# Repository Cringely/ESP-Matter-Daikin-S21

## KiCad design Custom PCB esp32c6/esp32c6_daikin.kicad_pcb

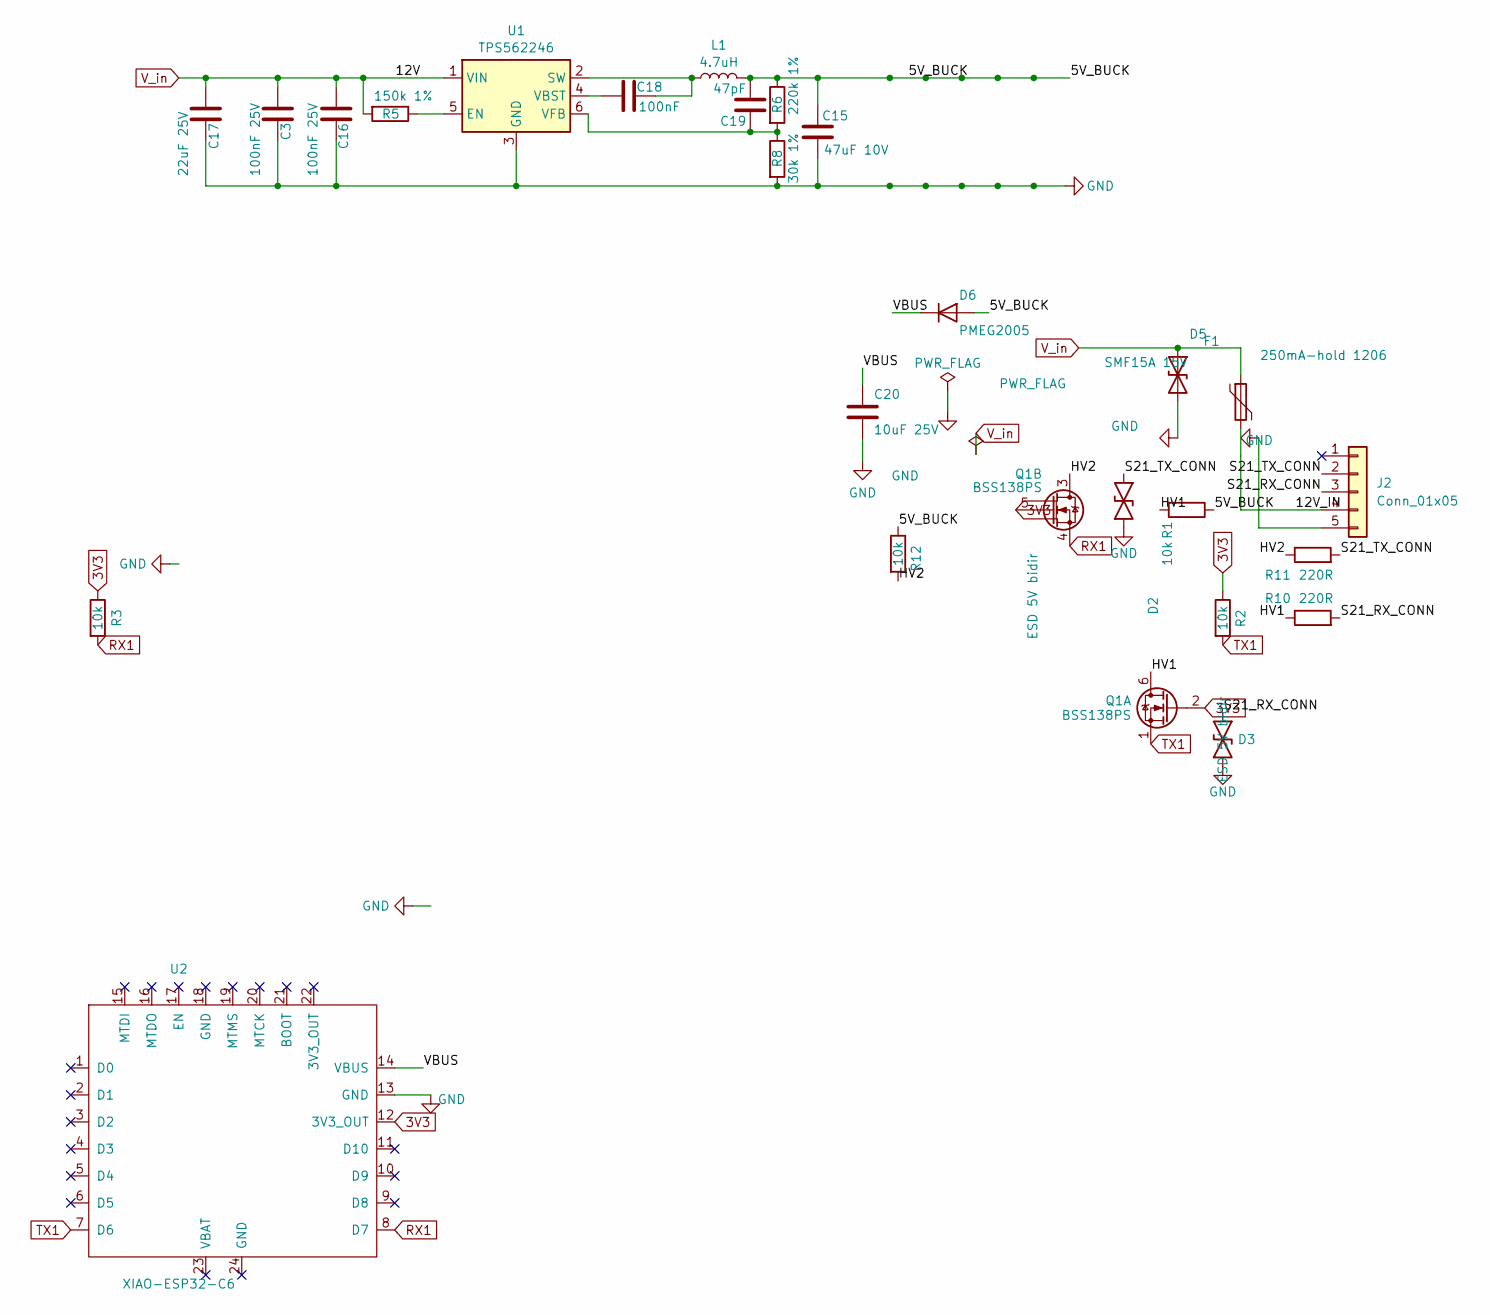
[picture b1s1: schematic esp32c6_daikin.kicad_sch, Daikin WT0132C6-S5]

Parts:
C3, C16: 100nF 25V; C0402; LCSC C307331
C15: 47uF 10V; C0805; LCSC C2292827
C17: 22uF 25V; C0805; LCSC C398931
C18: 100nF; C0402; LCSC C1525
C19: 47pF; C0402; LCSC C84706
C20: 10uF 25V; C0805; LCSC C15850
D2, D3: ESD 5V bidir; DFN1006-2L_L1.0-W0.6-P0.65-BI; MPN C5137770; LCSC C5137770
D5: SMF15A 15V; D_SOD-123F; LCSC C123802
D6: PMEG2005; D_SOD-123; LCSC C96233
F1: 250mA-hold 1206; Fuse_1206_3216Metric; LCSC C99561
J2: Conn_01x05; JST_EH_S5B-EH_1x05_P2.50mm_Horizontal; LCSC C265103
L1: 4.7uH; IND-SMD_L4.9-W4.9_NRS50XX; LCSC C307876
Q1: BSS138PS; SOT-363_L2.0-W1.3-P0.65-LS2.1-BR; MPN C193381; LCSC C193381
R1, R2, R12: 10k; R0402; MPN C25744; LCSC C25744
R3: 10k; R0402; LCSC C25744
R5: 150k 1%; R0603; LCSC C22807
R6: 220k 1%; R0603; LCSC C22961
R8: 30k 1%; R0402; LCSC C138008
R10, R11: 220R; R_0603_1608Metric; LCSC C1226
U1: TPS562246; SOT-5X3-6_L1.6-W1.2-P0.50-LS1.6-BR; LCSC C41833479
U2: XIAO-ESP32-C6; XIAO-ESP32-C6-DIP

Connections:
3V3: Q1.2 (GN), Q1.5 (GP), R2.1, R3.1, U2.12 (3V3_OUT)
/5V_BUCK: C15.1, C19.2, D6.2 (A), L1.2, R1.1, R6.1, R12.1
/12V_IN: F1.2, J2.4
/HV1: Q1.6 (DN), R1.2, R10.1
/HV2: Q1.3 (SP), R11.1, R12.2
/S21_RX_CONN: D3.2, J2.3, R10.2
/S21_TX_CONN: D2.2, J2.2, R11.2
/VBUS: C20.1, D6.1 (K), U2.14 (VBUS)
GND: C3.2, C15.2, C16.2, C17.2, C20.2, D2.1, D3.1, D5.2 (A2), J2.5, R8.2, U1.3 (GND), U2.13 (GND)
unnamed: R5.1, U1.5 (EN)
unnamed: C18.2, L1.1, U1.2 (SW)
unnamed: C18.1, U1.4 (VBST)
unnamed: C19.1, R6.2, R8.1, U1.6 (VFB)
RX1: Q1.4 (DP), R3.2, U2.8 (D7)
TX1: Q1.1 (SN), R2.2, U2.7 (D6)
V_in: C3.1, C16.1, C17.1, D5.1 (A1), F1.1, R5.2, U1.1 (VIN)

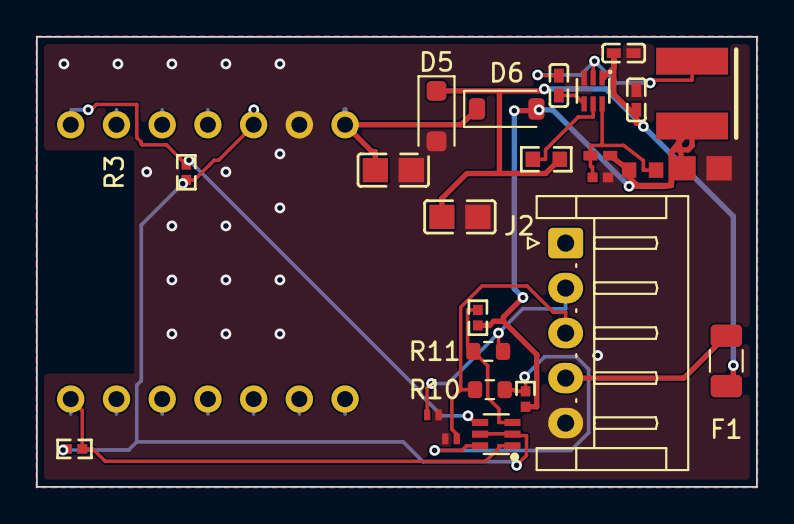
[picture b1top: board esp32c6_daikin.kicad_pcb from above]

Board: 2 copper layers, 40.0 x 25.0 mm, 26 parts (1 on the bottom side), 16 nets.

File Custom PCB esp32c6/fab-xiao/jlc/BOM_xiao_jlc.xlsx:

Comment | Designator | Footprint | LCSC Part #
100nF 50V X7R | C3,C16 | 0402 | C307331
22uF 25V X5R | C17 | 0805 | C45783
100nF 16V X7R | C18 | 0402 | C1525
47uF 10V X5R | C15 | 0805 | C2292827
47pF 50V C0G | C19 | 0402 | C1567
10uF 25V X5R | C20 | 0805 | C15850
ESD 5V bidir | D2,D3 | DFN1006-2L | C7420372
SMF15A 15V unidir TVS | D5 | SOD-123FL | C19077509
Schottky 20V 0.5A | D6 | SOD-123F | C7502707
PTC 250mA hold | F1 | 1206 | C99561
JST EH 1x05 2.5mm R/A | J2 | JST_EH_S5B-EH_1x05_P2.50mm_Horizontal | C265103
4.7uH 3.2A | L1 | 5045 (5.0x5.0mm) | C307876
BSS138PS dual N-ch | Q1 | SOT-363 | C193381
10k 1% | R1,R2,R3,R12 | 0402 | C25744
150k 1% | R5 | 0603 | C22807
220k 1% | R6 | 0603 | C22961
30k 1% | R8 | 0402 | C25776
220R 5% | R10,R11 | 0603 | C22962
TPS562246 | U1 | SOT-563 (SOT-5x3-6) | C41833479
